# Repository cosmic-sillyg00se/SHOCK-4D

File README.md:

#SHOCK 4D
(2/4/2026) WIth the help of HATSUNE MIKU we are GONG to make this datalogger work! It has no fancy features apart from a potental servo controller expansion, and is otherwise just a boring datalogger that I designed very very carefully to get something working at least... (four layers probably wasn't necesary for this but I really wanted to be safe...

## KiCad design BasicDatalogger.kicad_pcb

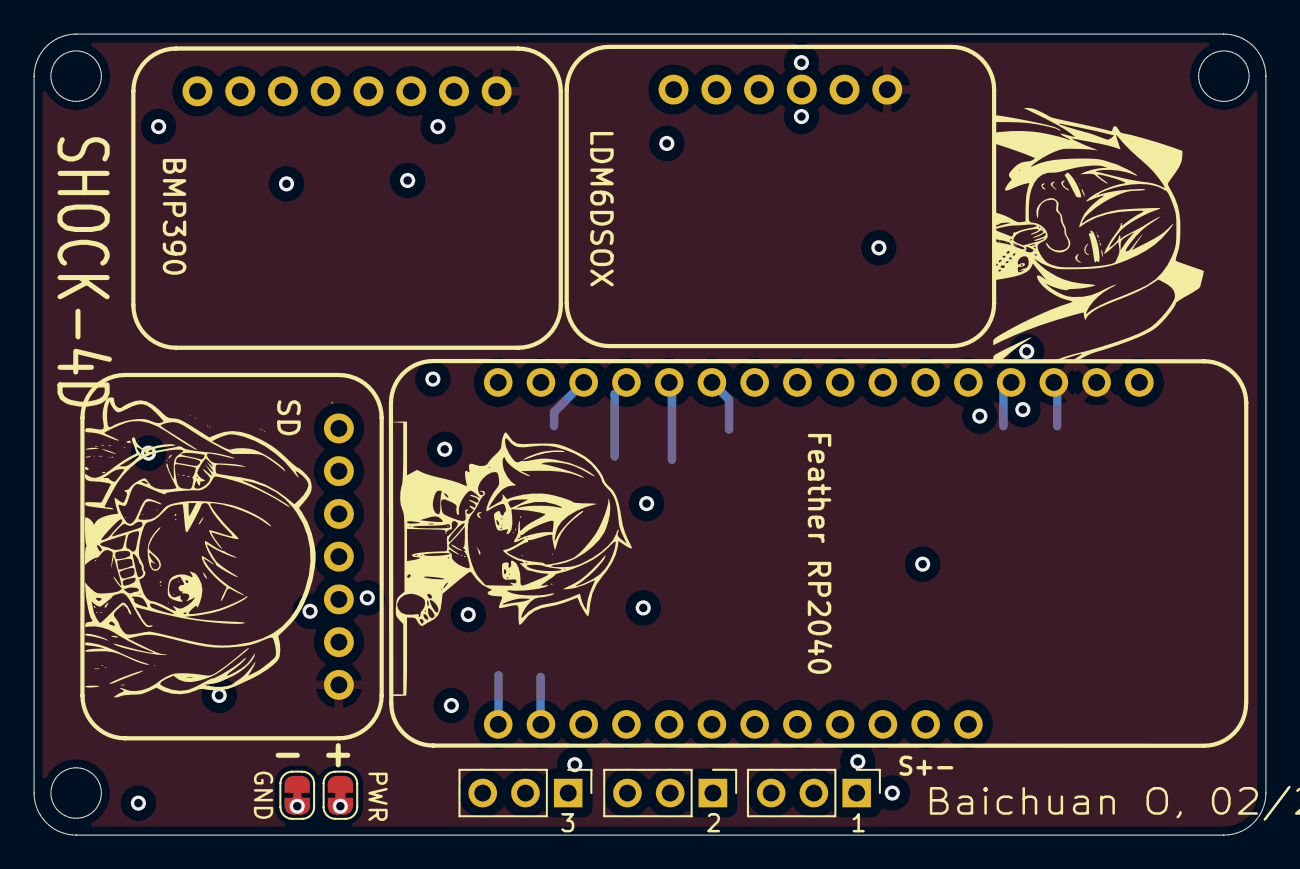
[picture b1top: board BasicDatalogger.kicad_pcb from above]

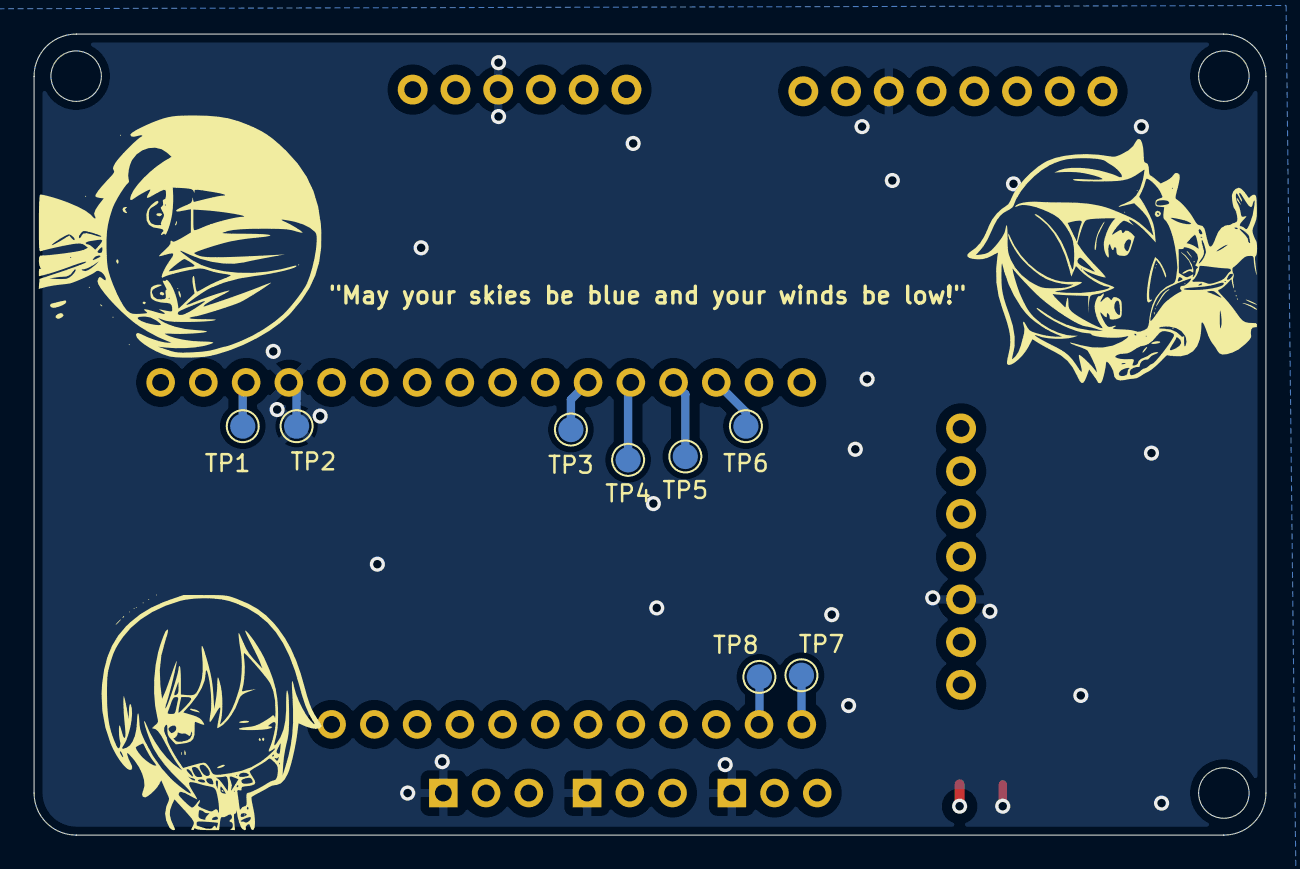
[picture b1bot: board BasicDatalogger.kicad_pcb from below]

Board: 4 copper layers, 73.2 x 47.6 mm, 17 parts (8 on the bottom side), 12 nets.

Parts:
1, 2, 3: Conn_01x03_Pin; PinHeader_1x03_P2.54mm_Vertical
GND: SolderJumper_2_Open; SolderJumper-2_P1.3mm_Open_RoundedPad1.0x1.5mm
PWR: SolderJumper_2_Open; SolderJumper-2_P1.3mm_Open_RoundedPad1.0x1.5mm
TP1, TP2, TP3, TP4, TP5, TP6, TP7, TP8: TestPoint; TestPoint_Pad_D1.5mm
U1: Adafruit-Feather-RP2040
U2: BMP390
U3: LSM6DSOX + LIS3MDL
U4: SD Breakout

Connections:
/3V3: TP1.1, U1.2 (3.3V), U1.3 (3.3V), U2.1 (VIN), U3.1 (VIN), U4.1 (VIN)
/CS: TP6.1, U1.14 (RX/CS/GPIO1), U4.7 (CS)
/GND: 1.1, 2.1, 3.1, GND.1 (A), GND.2 (B), TP2.1, U1.4 (GND), U2.3 (GND), U3.3 (GND), U4.3 (GND)
/MISO: TP5.1, U1.13 (MISO/GPIO20), U4.5 (MISO)
/MOSI: TP4.1, U1.12 (MOSI/GPIO19), U4.6 (MOSI)
/PWR: 1.2, 2.2, 3.2, PWR.1 (A), PWR.2 (B)
/S1: 3.3, U1.19 (D5/GPIO7)
/S2: 2.3, U1.20 (D6/GPIO8)
/S3: 1.3, U1.21 (D9/GPIO9)
/SCK: TP3.1, U1.11 (SCK/GPIO18), U4.4 (SCK)
/SCL: TP8.1, U1.18 (SCL/GPIO3), U2.4 (SCL), U3.4 (SCL)
/SDA: TP7.1, U1.17 (SDA/GPIO2), U2.6 (SDA), U3.5 (SDA)

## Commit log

2026-02-05 Better REEADME
2026-02-05 Uploaded KiCad Files
2026-02-06 General update
